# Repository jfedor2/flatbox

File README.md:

# Flatbox: Low profile hitbox-layout fightstick

This repository contains 3D-printable models, PCB design files and code needed to make an arcade controller that looks like this:

There are ten major versions of the Flatbox. They all use Kailh low profile (choc v1) mechanical keyboard switches. The table below lists their main features. See the README for each version for details on how to make them.

version | case dimensions (mm) | compatibility | add-on board | onboard chip | SMT assembly required | firmware
------- | --------------- | ------------- | ------------ | ------------ | --------------------- | --------
[rev1.1](hardware-rev1.1) | 218x128x10 | PC, PS3 | Arduino Pro Micro | - | no | [ATmega32U4](firmware-atmega32u4)
[rev2](hardware-rev2) | 218x130x10 | PC, PS3 | - | ATmega32U4 | yes | [ATmega32U4](firmware-atmega32u4)
[rev3](hardware-rev3) | 218x130x10 | PC, PS3, PS4 or PC, Switch, PS3, PS4, PS5\* | [Brook PS3/PS4](https://www.brookaccessory.com/detail/58690501/) or [P5 mini](https://www.brookaccessory.com/detail/92299183/) | - | yes | [Brook](https://www.brookaccessory.com/download/)
[rev4.1](hardware-rev4.1) | 218x130x11 | PC, PS3, PS4\*, PS5\*, Switch | - | RP2040 | yes | [GP2040-CE](https://gp2040-ce.info/)
[rev5](hardware-rev5) | 218x126x10 | PC, PS3, PS4\*, Switch | [RP2040-Zero](https://www.waveshare.com/rp2040-zero.htm) | - | no | [GP2040-CE](https://gp2040-ce.info/)
[rev6](hardware-rev6) | 218x126x10 | PC, Switch | - | CH552T | yes | [CH552](firmware-ch552)
[rev7.2](hardware-rev7.2) | 218x130x11 | PC, Switch | [Xiao nRF52840 Plus](https://www.seeedstudio.com/Seeed-Studio-XIAO-nRF52840-Plus-p-6359.html) | - | no | [PGF](https://github.com/jfedor2/portable-gamepad-firmware)
[rev8](hardware-rev8) | 218x130x11 | PC, PS3, PS4\*, PS5\*, Switch | - | RP2350 | yes | [GP2040-CE](https://gp2040-ce.info/)
[rev9](hardware-rev9) | 218x130x11 | PC, Switch | - | SAMD21 | yes | [PGF](https://github.com/jfedor2/portable-gamepad-firmware)
[rev10](hardware-rev10) | 218x130x11 | PC, Switch | - | STM32G0B1 | yes | [PGF](https://github.com/jfedor2/portable-gamepad-firmware)

\* - with caveats

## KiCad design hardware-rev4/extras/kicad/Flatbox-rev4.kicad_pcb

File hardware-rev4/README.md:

# Flatbox rev4

_**Please note**: There's a newer version of this Flatbox variant: [rev4.1](../hardware-rev4.1). If you're starting fresh, it's probably better to make that one._

This is rev4 of the Flatbox. In this version the PCB includes a microcontroller and USB port. Everything is built in, you only have to add the switches (and flash the firmware).

To make one you will need:

* [3D printed case parts](3d-printed-case) - top and bottom
* [the PCB](pcb)
* 12x Kailh low profile (choc v1) switches of your choice
* (optionally) 12x Kailh low profile hotswap sockets
* [3D printed buttoncaps](../3d-printed-buttoncaps)
* 6x 6x6x5mm tact switches
* 7x 3x10mm wood screws
* some kind of rubber feet or non-slip padding for the bottom
* a soldering iron

I printed the case at 0.20mm layer height. The top part should be printed upside-down, the bottom part should be printed as-is. They don't require supports.

I used [JLCPCB](https://jlcpcb.com/) to make the PCB and assemble the SMD parts. The [included files](pcb) can be used with JLCPCB directly. If you want to use some other service, check the file formats that they expect. When ordering from JLCPCB, upload the Gerber zip, leave all the settings at default (you can choose the PCB color), then select "SMT Assembly" and upload the BOM and CPL files. PCB thickness should be 1.6mm.

The PCB you get from JLCPCB will look like this:

The switches can be soldered in directly to the PCB or you can use hotswap sockets. If you want to use hotswap sockets, you will have to print the appropriate bottom part of the case (it's 1mm thicker).

For the firmware you probably want to use [GP2040-CE](https://gp2040-ce.info/). Go to the [GP2040-CE downloads page](https://gp2040-ce.info/downloads/) and get the UF2 file for Flatbox rev4.

To flash the firmware, connect the PCB to a computer with a USB cable, then press the RESET button while holding the BOOT button on the PCB. A drive named "RPI-RP2" should appear. Copy the UF2 file you downloaded to that drive. That's it.

(Of course you can also use any other RP2040-compatible firmware if you want.)

PCB design licensed under [CC BY-SA 4.0](https://creativecommons.org/licenses/by-sa/4.0/).

PCB design uses the following libraries:

* [keyswitches.pretty](https://github.com/daprice/keyswitches.pretty) by [daprice](https://github.com/daprice) ([CC BY-SA 4.0](https://creativecommons.org/licenses/by-sa/4.0/))
* [Type-C.pretty](https://github.com/ai03-2725/Type-C.pretty) by [ai03-2725](https://github.com/ai03-2725)
* RP2040 library from the [minimal design example](https://datasheets.raspberrypi.org/rp2040/Minimal-KiCAD.zip) from the [Hardware design with RP2040](https://datasheets.raspberrypi.org/rp2040/hardware-design-with-rp2040.pdf) document

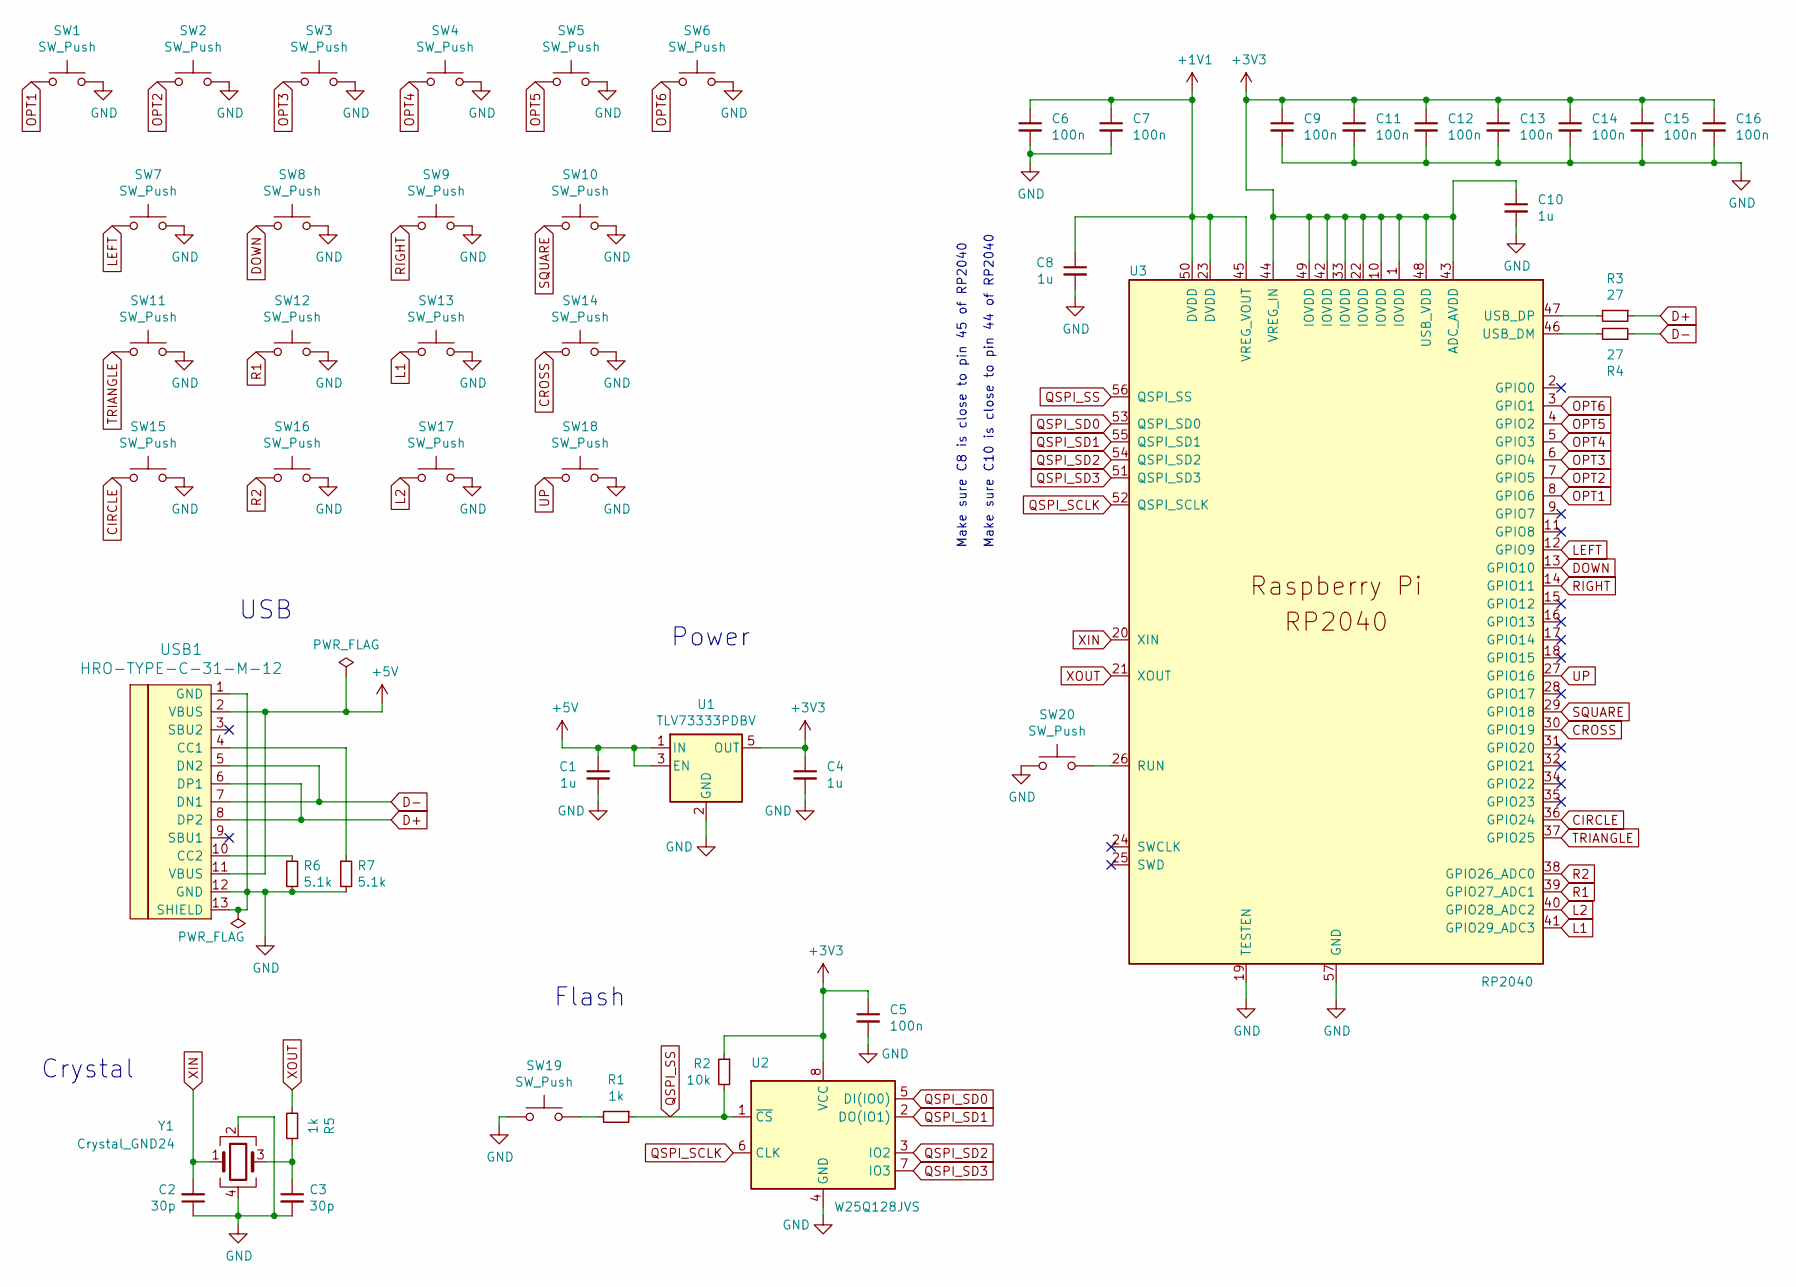
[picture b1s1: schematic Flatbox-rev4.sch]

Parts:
C1, C4, C8, C10: 1u; C_0402_1005Metric; LCSC C52923
C2, C3: 30p; C_0402_1005Metric; LCSC C1570
C5, C6, C7, C9, C11, C12, C13, C14, C15, C16: 100n; C_0402_1005Metric; LCSC C1525
R1, R5: 1k; R_0402_1005Metric; LCSC C11702
R2: 10k; R_0402_1005Metric; LCSC C25744
R3, R4: 27; R_0402_1005Metric; LCSC C138021
R6, R7: 5.1k; R_0402_1005Metric; LCSC C25905
SW1, SW2, SW3, SW4, SW5, SW6: SW_Push; SW_PUSH_6mm_H5mm
SW7, SW8, SW9, SW10, SW11, SW12, SW13, SW14, SW15, SW16, SW17, SW18: SW_Push; Kailh_socket_PG1350_optional
SW19, SW20: SW_Push; SW_SPST_Omron_B3FS-100xP; LCSC C271750
U1: TLV73333PDBV; SOT-23-5; LCSC C134139
U2: W25Q128JVS; SOIC-8_5.23x5.23mm_P1.27mm; LCSC C97521
U3: RP2040; RP2040-QFN-56; LCSC C2040
USB1: HRO-TYPE-C-31-M-12; HRO-TYPE-C-31-M-12-Assembly; LCSC C165948
Y1: Crystal_GND24; Crystal_SMD_3225-4Pin_3.2x2.5mm; LCSC C9002

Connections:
+1V1: C6.1, C7.1, C8.1, U3.23 (DVDD), U3.45 (VREG_VOUT), U3.50 (DVDD)
+3V3: C4.1, C5.1, C9.1, C10.1, C11.1, C12.1, C13.1, C14.1, C15.1, C16.1, R2.1, U1.5 (OUT), U2.8 (VCC), U3.1 (IOVDD), U3.10 (IOVDD), U3.22 (IOVDD), U3.33 (IOVDD), U3.42 (IOVDD), U3.43 (ADC_AVDD), U3.44 (VREG_IN), U3.48 (USB_VDD), U3.49 (IOVDD)
+5V: C1.1, U1.1 (IN), U1.3 (EN), USB1.2 (VBUS), USB1.11 (VBUS)
CIRCLE: SW15.1, U3.36 (GPIO24)
CROSS: SW14.1, U3.30 (GPIO19)
D+: R3.1, USB1.6 (DP1), USB1.8 (DP2)
D-: R4.1, USB1.5 (DN2), USB1.7 (DN1)
DOWN: SW8.1, U3.13 (GPIO10)
GND: C1.2, C2.1, C3.2, C4.2, C5.2, C6.2, C7.2, C8.2, C9.2, C10.2, C11.2, C12.2, C13.2, C14.2, C15.2, C16.2, R6.2, R7.2, SW1.2, SW2.2, SW3.2, SW4.2, SW5.2, SW6.2, SW7.2, SW8.2, SW9.2, SW10.2, SW11.2, SW12.2, SW13.2, SW14.2, SW15.2, SW16.2, SW17.2, SW18.2, SW19.1, SW20.1, U1.2 (GND), U2.4 (GND), U3.19 (TESTEN), U3.57 (GND), USB1.1 (GND), USB1.12 (GND), USB1.13 (SHIELD), Y1.2, Y1.4
L1: SW13.1, U3.41 (GPIO29_ADC3)
L2: SW17.1, U3.40 (GPIO28_ADC2)
LEFT: SW7.1, U3.12 (GPIO9)
unnamed: C3.1, R5.1, Y1.3
unnamed: R1.2, SW19.2
unnamed: R3.2, U3.47 (USB_DP)
unnamed: R4.2, U3.46 (USB_DM)
unnamed: R6.1, USB1.10 (CC2)
unnamed: R7.1, USB1.4 (CC1)
unnamed: SW20.2, U3.26 (RUN)
OPT1: SW1.1, U3.8 (GPIO6)
OPT2: SW2.1, U3.7 (GPIO5)
OPT3: SW3.1, U3.6 (GPIO4)
OPT4: SW4.1, U3.5 (GPIO3)
OPT5: SW5.1, U3.4 (GPIO2)
OPT6: SW6.1, U3.3 (GPIO1)
QSPI_SCLK: U2.6 (CLK), U3.52 (QSPI_SCLK)
QSPI_SD0: U2.5 (DI(IO0)), U3.53 (QSPI_SD0)
QSPI_SD1: U2.2 (DO(IO1)), U3.55 (QSPI_SD1)
QSPI_SD2: U2.3 (IO2), U3.54 (QSPI_SD2)
QSPI_SD3: U2.7 (IO3), U3.51 (QSPI_SD3)
QSPI_SS: R1.1, R2.2, U2.1 (~CS), U3.56 (QSPI_SS)
R1: SW12.1, U3.39 (GPIO27_ADC1)
R2: SW16.1, U3.38 (GPIO26_ADC0)
RIGHT: SW9.1, U3.14 (GPIO11)
SQUARE: SW10.1, U3.29 (GPIO18)
TRIANGLE: SW11.1, U3.37 (GPIO25)
UP: SW18.1, U3.27 (GPIO16)
XIN: C2.2, U3.20 (XIN), Y1.1
XOUT: R5.2, U3.21 (XOUT)

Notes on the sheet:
Make sure C10 is close to pin 44 of RP2040
Crystal
Power
USB
Make sure C8 is close to pin 45 of RP2040
Flash

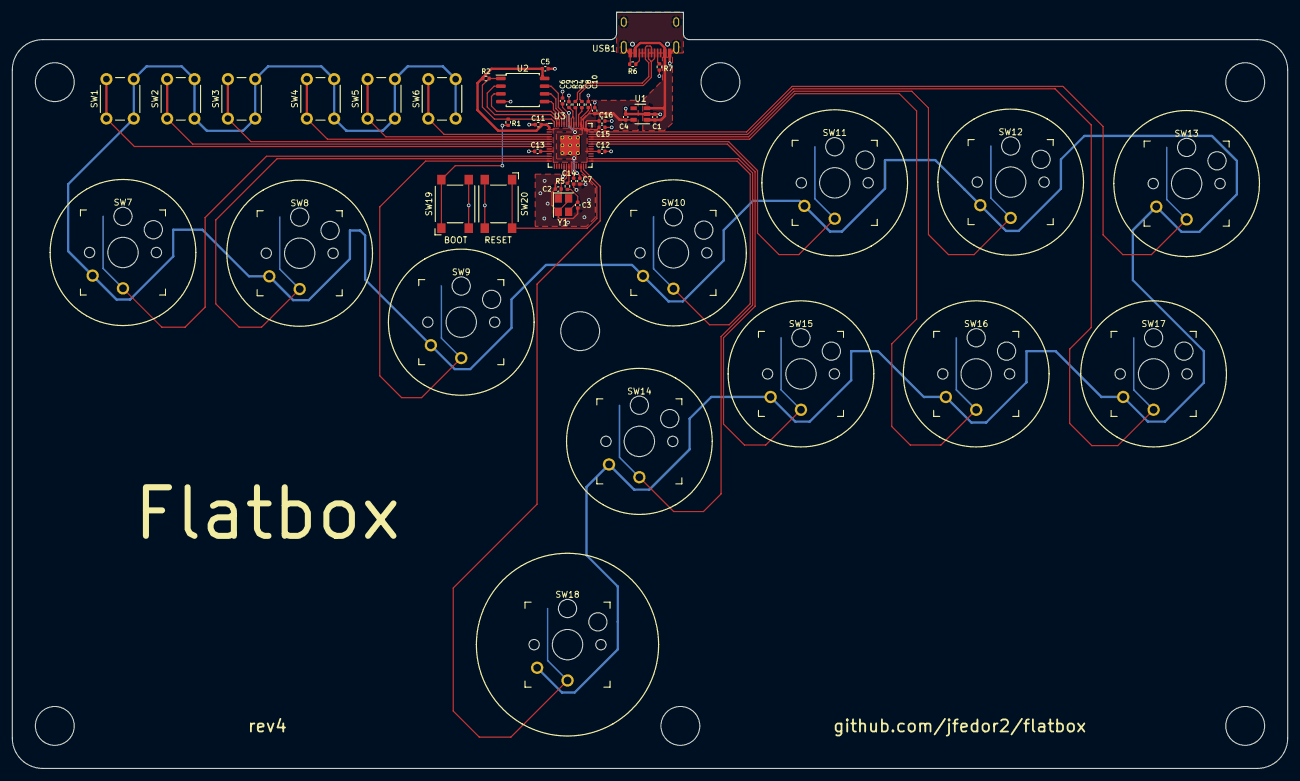
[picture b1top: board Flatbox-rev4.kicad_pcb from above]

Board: 2 copper layers, 210.0 x 124.5 mm, 48 parts (0 on the bottom side), 39 nets.

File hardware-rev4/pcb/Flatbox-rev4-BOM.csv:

Comment,Designator,Footprint,LCSC
"30p","C2,C3","Capacitor_SMD:C_0402_1005Metric","C1570"
"1u","C1,C4,C8,C10","Capacitor_SMD:C_0402_1005Metric","C52923"
"100n","C5,C6,C7,C9,C11,C12,C13,C14,C15,C16","Capacitor_SMD:C_0402_1005Metric","C1525"
"10k","R2","Resistor_SMD:R_0402_1005Metric","C25744"
"27","R3,R4","Resistor_SMD:R_0402_1005Metric","C138021"
"1k","R1,R5","Resistor_SMD:R_0402_1005Metric","C11702"
"5.1k","R6,R7","Resistor_SMD:R_0402_1005Metric","C25905"
"SW_Push","SW1,SW2,SW3,SW4,SW5,SW6","Button_Switch_THT:SW_PUSH_6mm_H5mm",""
"SW_Push","SW19,SW20","Button_Switch_SMD:SW_SPST_Omron_B3FS-100xP","C271750"
"SW_Push","SW7,SW8,SW9,SW10,SW11,SW12,SW13,SW14,SW15,SW16,SW17,SW18","Kailh:Kailh_socket_PG1350_optional",""
"TLV73333PDBV","U1","Package_TO_SOT_SMD:SOT-23-5","C134139"
"W25Q128JVS","U2","Package_SO:SOIC-8_5.23x5.23mm_P1.27mm","C97521"
"RP2040","U3","RP2040:RP2040-QFN-56","C2040"
"HRO-TYPE-C-31-M-12","USB1","Type-C:HRO-TYPE-C-31-M-12-Assembly","C165948"
"Crystal_GND24","Y1","Crystal:Crystal_SMD_3225-4Pin_3.2x2.5mm","C9002"

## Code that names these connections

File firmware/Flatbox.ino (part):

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#define PIN_DOWN      7
#define PIN_LEFT      6
#define PIN_RIGHT     8
#define PIN_CROSS     10
#define PIN_CIRCLE    14
#define PIN_TRIANGLE  15
#define PIN_SQUARE    16
#define PIN_L1        21
#define PIN_L2        20
#define PIN_R1        19
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#define PIN_DOWN      9
#define PIN_LEFT      8
#define PIN_RIGHT     10
#define PIN_CROSS     18
#define PIN_CIRCLE    21
#define PIN_TRIANGLE  14
#define PIN_SQUARE    7
#define PIN_L1        15
#define PIN_L2        19
#define PIN_R1        16
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  pinMode(PIN_DOWN, INPUT_PULLUP);
  pinMode(PIN_LEFT, INPUT_PULLUP);
  pinMode(PIN_RIGHT, INPUT_PULLUP);
  pinMode(PIN_CROSS, INPUT_PULLUP);
  pinMode(PIN_CIRCLE, INPUT_PULLUP);
  pinMode(PIN_TRIANGLE, INPUT_PULLUP);
  pinMode(PIN_SQUARE, INPUT_PULLUP);
  pinMode(PIN_L1, INPUT_PULLUP);
  pinMode(PIN_L2, INPUT_PULLUP);
  pinMode(PIN_R1, INPUT_PULLUP);
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       digitalRead(PIN_LEFT) == LOW,
       digitalRead(PIN_RIGHT) == LOW);

  if (digitalRead(PIN_SQUARE) == LOW) {
    report.buttons |= 1 << 0;
    report.squareAxis = 0xff;
  }
  if (digitalRead(PIN_CROSS) == LOW) {
    report.buttons |= 1 << 1;
    report.crossAxis = 0xff;
  }
  if (digitalRead(PIN_CIRCLE) == LOW) {
    report.buttons |= 1 << 2;
    report.circleAxis = 0xff;
  }
  if (digitalRead(PIN_TRIANGLE) == LOW) {
    report.buttons |= 1 << 3;
    report.triangleAxis = 0xff;
  }
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
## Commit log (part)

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2021-08-16 Initial commit
    This repository's history has been rewritten. Sorry about that.
2021-09-02 Add rev1.1
2021-09-02 Add rev3
2021-09-02 Update README with rev1.1 and rev3
2021-09-21 Add rev4
2021-09-21 Update README with rev4
2021-09-21 firmware -> firmware-atmega32u4
    Rename "firmware" directory to "firmware-atmega32u4", now that we also
    have RP2040 firmware.
2021-09-22 Add KiCad files
2022-01-12 Add STEP files for case designs
2022-11-10 Update buttoncap models
    Previously buttoncaps had the stems stick out 4mm, new ones stick out
    3mm. This should allow the buttoncap to properly rest on the surface
    of the switch.
2022-11-10 Add rev5
    Rev5 uses an RP2040-Zero board as an add-on. The Flatbox rev5 PCB
    doesn't need SMT assembly.
2022-11-21 Build both rev4 and rev5
    Adds separate targets for rev4 and rev5 to CMakeLists.txt so that both
    are built and you don't have to mess with manually changing defines.
2022-11-21 Better compatibility with flash chips
    When building firmware for rev4 and rev5, use slower settings for
    flash that should give better compatibility with different chips or
    even samples of the same chip.
    #define PICO_XOSC_STARTUP_DELAY_MULTIPLIER 64
    #define PICO_BOOT_STAGE2_CHOOSE_GENERIC_03H 1
    #define PICO_FLASH_SPI_CLKDIV 4
2022-11-23 Remove duplicate entry in CMakeLists.txt
2022-11-23 Revert flash speed changes, leave only xosc
    Previous commit changed three board settings in hopes of improving
    compatibility with some rev4 hardware. One of them applied to the
    crystal oscillator and two to the flash chip. After some more tests in
    the field, I now think only the crystal was problematic so this
    reverts the flash speed changes.
    They didn't necessarily hurt anything and let's keep them in mind in
2022-11-27 extract kicad to track changes
2022-11-27 ignore cache file
2022-11-27 ignore backups
2022-11-27 expand center pin to 5mm to partially support choc v2 switch, refill zone
2022-11-27 timestamps from gerber export
2022-11-27 update gerber
2022-11-27 update README for choc v2 pin removal
2023-02-11 Updated button STL files - Stems shortened by 0.5 mm - Walls extended by 3 mm
2023-08-11 rev 5b (#3)
    * Proposed Rev 5B
2023-08-12 add images and update associated readme
2023-08-12 correct typo
2023-08-14 Add links to GP2040-CE
    Most people will want to use the GP2040-CE firmware with the rev4 and
    rev5.
    This commit adds links to the GP2040-CE website in the READMEs and
    removes the precompiled UF2 files of our own firmware to avoid
    confusion.
    (The source code for our firmware is still there.)
2023-09-04 Add rev5 CNC machined case
2023-09-06 Add mention of top-site nuts in list of materials
2023-09-21 Add hotswap versions of case STEP files
2024-05-22 Add info on Brook P5 mini Fighting Board
2024-05-22 Update GP2040-CE downloads URL
2024-05-22 Add rev6
2024-06-25 Add rev7
2025-03-24 Add rev4.1
2025-03-25 Add rev8
